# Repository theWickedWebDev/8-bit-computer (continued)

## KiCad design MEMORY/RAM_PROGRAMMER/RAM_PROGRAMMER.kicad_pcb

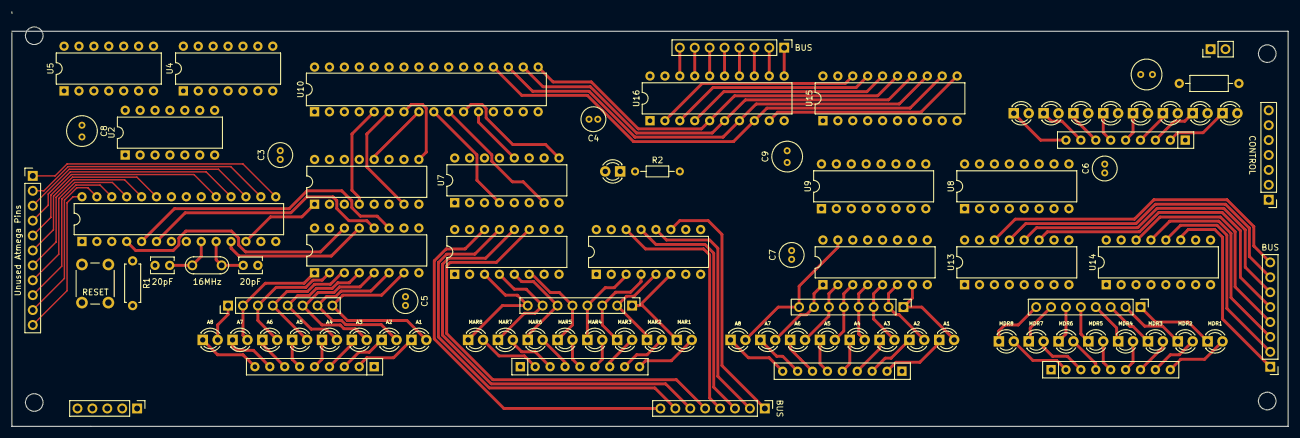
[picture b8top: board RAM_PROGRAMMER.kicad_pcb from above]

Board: 4 copper layers, 217.4 x 70.6 mm, 89 parts (0 on the bottom side), 157 nets.

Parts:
C1, C2: C_Small; C_Disc_D3.8mm_W2.6mm_P2.50mm
C3, C4, C5, C6, C7: CP1; C_Radial_D4.0mm_H5.0mm_P1.50mm
C8, C9, C10: CP_Small; C_Radial_D5.0mm_H7.0mm_P2.00mm
D1, D2, D3, D4, D5, D6, D7, D8, D9, D10, D11, D12, D13, D14, D15, D16, D17, D18, D19, D20, D21, D22, D23, D24, D25, D26, D27, D28, D29, D30, D31, D32, D33, D34, D35, D36, D37, D38, D39, D40, D41: LED; LED_D3.0mm
J1: Conn_01x02; PinHeader_1x02_P2.54mm_Vertical
J2: Conn_01x07; PinHeader_1x07_P2.54mm_Vertical
J3, J4, J5, J8, J9, J10, J11: Conn_01x08; PinHeader_1x08_P2.54mm_Vertical
J6: Conn_01x05; PinHeader_1x05_P2.54mm_Vertical
J7: Conn_01x11; PinHeader_1x11_P2.54mm_Vertical
R1: R_Small_US; R_Axial_DIN0207_L6.3mm_D2.5mm_P7.62mm_Horizontal
R2: R_Small_US; R_Axial_DIN0204_L3.6mm_D1.6mm_P7.62mm_Horizontal
R4: R_Small_US; R_Axial_DIN0207_L6.3mm_D2.5mm_P10.16mm_Horizontal
RN1, RN2, RN3, RN4, RN5: R_Network08_US; R_Array_SIP9
SW1: SW_Push; SW_PUSH_6mm
U1: ATmega328-PU; DIP-28_W7.62mm
U2: 74LS04; DIP-14_W7.62mm
U3, U17: 74HC595; DIP-16_W7.62mm
U4: 74LS32; DIP-14_W7.62mm
U5: 74LS08; DIP-14_W7.62mm
U6, U7, U8, U9: 74LS157; DIP-16_W7.62mm
U10: IS61C1024-15N; DIP-32_W7.62mm
U11, U12, U13, U14: 74LS173; DIP-16_W7.62mm
U15, U16: 74LS245; DIP-20_W7.62mm
Y1: Crystal; Resonator-2Pin_W7.0mm_H2.5mm

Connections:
+5V: C3.1, C4.1, C5.1, C6.1, C7.1, J1.2, R1.1, U1.7, U1.20, U3.10, U3.16, U6.16, U7.16, U8.16, U9.16, U10.30, U10.32, U15.1, U15.20, U16.1, U16.20, U17.10, U17.16
/ACTIVE: J6.1, U1.14
/CLOCK: J2.1, U5.1, U11.7, U12.7, U13.7, U14.7
/ENABLE_RAM_WRITE_PROG: U1.12, U4.2, U6.1, U7.1, U8.1, U9.1
/MAR_IN: J2.4, U11.9, U11.10, U12.9, U12.10
/MAR_RST: J2.5, U11.15, U12.15
/MEM_IN: J2.6, U13.9, U13.10, U14.9, U14.10
/MEM_RST: J2.7, R4.1, U13.15, U14.15
/RAM_OUT: J2.3, U16.19
/RAM_WE: J2.2, U5.2
/RESET: J6.4, R1.2, SW1.2, U1.1
/RX: J6.2, U1.2
/SH_CLK: U1.5, U3.11
/SH_DATA: U1.4, U3.14, U17.11
/SH_LATCH: U1.6, U3.12, U17.12
/SH_OE: U1.11, U3.13, U17.13
/TX: J6.3, U1.3
GND: C1.1, C2.1, C3.2, C4.2, C5.2, C6.2, C7.2, C8.2, C9.2, C10.2, J1.1, J6.5, R2.2, R4.2, RN1.1, RN2.1, RN3.1, RN4.1, RN5.1, SW1.1, U1.8, U1.22, U2.7, U3.8, U4.7, U6.8, U6.15, U7.8, U7.15, U8.8, U8.15, U9.8, U9.15, U10.2, U10.3, U10.4, U10.16, U10.22, U10.23, U10.25, U10.26, U10.27, U10.28, U10.31, U11.1, U11.2, U11.8, U12.1, U12.2, U12.8, U13.1, U13.2, U13.8, U14.1, U14.2, U14.8, U15.10, U16.10, U17.8
unnamed: C1.2, U1.9, Y1.1
unnamed: C2.2, U1.10, Y1.2
unnamed: D1.1, J5.8, U6.2, U11.3
unnamed: D1.2, RN1.2
unnamed: D2.1, J5.7, U6.5, U11.4
unnamed: D2.2, RN1.3
unnamed: D3.1, J5.6, U6.11, U11.5
unnamed: D3.2, RN1.4
unnamed: D4.1, J5.5, U6.14, U11.6
unnamed: D4.2, RN1.5
unnamed: D5.1, J5.4, U7.2, U12.3
unnamed: D5.2, RN1.6
unnamed: D6.1, J5.3, U7.5, U12.4
unnamed: D6.2, RN1.7
unnamed: D7.1, J5.2, U7.11, U12.5
unnamed: D7.2, RN1.8
unnamed: D8.1, J5.1, U7.14, U12.6
unnamed: D8.2, RN1.9
unnamed: D9.1, RN2.2
unnamed: D9.2, U10.21, U15.11, U16.9
unnamed: D10.1, RN3.9
unnamed: D10.2, J4.1, U3.15, U7.13
unnamed: D11.1, RN2.3
unnamed: D11.2, U10.20, U15.12, U16.8
unnamed: D12.1, RN3.8
unnamed: D12.2, J4.2, U3.1, U7.10
unnamed: D13.1, RN2.4
unnamed: D13.2, U10.19, U15.13, U16.7
unnamed: D14.1, RN3.7
unnamed: D14.2, J4.3, U3.2, U7.6
unnamed: D15.1, RN2.5
unnamed: D15.2, U10.18, U15.14, U16.6
unnamed: D16.1, RN3.6
unnamed: D16.2, J4.4, U3.3, U7.3
unnamed: D17.1, RN2.6
unnamed: D17.2, U10.17, U15.15, U16.5
unnamed: D18.1, RN3.5
unnamed: D18.2, J4.5, U3.4, U6.13
unnamed: D19.1, RN2.7
unnamed: D19.2, U10.15, U15.16, U16.4
unnamed: D20.1, RN3.4
unnamed: D20.2, J4.6, U3.5, U6.10
unnamed: D21.1, RN2.8
unnamed: D21.2, U10.14, U15.17, U16.3
unnamed: D22.1, RN3.3
unnamed: D22.2, J4.7, U3.6, U6.6
unnamed: D23.1, RN2.9
unnamed: D23.2, U10.13, U15.18, U16.2
unnamed: D24.1, RN3.2
unnamed: D24.2, J4.8, U3.7, U6.3
unnamed: D25.1, R2.1
unnamed: D25.2, U2.2, U10.29, U15.19
unnamed: D26.1, J11.8, U9.14, U13.3
unnamed: D26.2, RN4.2
unnamed: D27.1, J11.7, U9.11, U13.4
unnamed: D27.2, RN4.3
unnamed: D28.1, J11.6, U9.5, U13.5
unnamed: D28.2, RN4.4
unnamed: D29.1, J11.5, U9.2, U13.6
unnamed: D29.2, RN4.5
unnamed: D30.1, J11.4, U8.14, U14.3
unnamed: D30.2, RN4.6
unnamed: D31.1, J11.3, U8.11, U14.4
unnamed: D31.2, RN4.7
unnamed: D32.1, J11.2, U8.5, U14.5
unnamed: D32.2, RN4.8
unnamed: D33.1, J11.1, U8.2, U14.6
unnamed: D33.2, RN4.9
unnamed: D34.1, RN5.9
unnamed: D34.2, J10.8, U9.13, U17.15
unnamed: D35.1, RN5.8
unnamed: D35.2, J10.7, U9.10, U17.1
unnamed: D36.1, RN5.7
unnamed: D36.2, J10.6, U9.6, U17.2
unnamed: D37.1, RN5.6
unnamed: D37.2, J10.5, U9.3, U17.3
unnamed: D38.1, RN5.5
unnamed: D38.2, J10.4, U8.13, U17.4
unnamed: D39.1, RN5.4
unnamed: D39.2, J10.3, U8.10, U17.5
unnamed: D40.1, RN5.3
unnamed: D40.2, J10.2, U8.6, U17.6
unnamed: D41.1, RN5.2
unnamed: D41.2, J10.1, U8.3, U17.7
unnamed: J3.1, U14.11
unnamed: J3.2, U14.12
unnamed: J3.3, U14.13
unnamed: J3.4, U14.14
unnamed: J3.5, U13.11
unnamed: J3.6, U13.12
unnamed: J3.7, U13.13
unnamed: J3.8, U13.14
unnamed: J7.1, U1.15
unnamed: J7.2, U1.16
unnamed: J7.3, U1.17
unnamed: J7.4, U1.18
unnamed: J7.5, U1.19
unnamed: J7.6, U1.23
unnamed: J7.7, U1.24
unnamed: J7.8, U1.25
unnamed: J7.9, U1.26
unnamed: J7.10, U1.27
unnamed: J7.11, U1.28
unnamed: J8.1, U12.11
unnamed: J8.2, U12.12
unnamed: J8.3, U12.13
unnamed: J8.4, U12.14
unnamed: J8.5, U11.11
unnamed: J8.6, U11.12
unnamed: J8.7, U11.13
unnamed: J8.8, U11.14
unnamed: J9.1, U16.11
unnamed: J9.2, U16.12
unnamed: J9.3, U16.13
unnamed: J9.4, U16.14
unnamed: J9.5, U16.15
unnamed: J9.6, U16.16
unnamed: J9.7, U16.17
unnamed: J9.8, U16.18
unnamed: U4.1, U5.3
unnamed: U6.4, U10.5
unnamed: U6.7, U10.6
unnamed: U6.9, U10.7
unnamed: U6.12, U10.8
unnamed: U7.4, U10.9
unnamed: U7.7, U10.10
unnamed: U7.9, U10.11
unnamed: U7.12, U10.12
unnamed: U2.1, U4.3, U10.24
unnamed: U9.12, U15.2
unnamed: U9.9, U15.3
unnamed: U9.7, U15.4
unnamed: U9.4, U15.5
unnamed: U8.12, U15.6
unnamed: U8.9, U15.7
unnamed: U8.7, U15.8
unnamed: U8.4, U15.9
unnamed: U3.9, U17.14
VCC: C8.1, C9.1, C10.1, U2.14, U4.14, U11.16, U12.16, U13.16, U14.16
